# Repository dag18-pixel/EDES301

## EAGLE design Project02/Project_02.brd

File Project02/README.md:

<h1>Etch-A-Sketch Project</h1>
TThis repository contains all implementation files for the Etch-a-Sketch project, including the final PCB layout and schematic, bill of materials (BOM), mechanical drawing, and all library files used. The goal of this project was to apply PCB design concepts from class using Autodesk software and to gain hands-on experience with the PCB manufacturing process

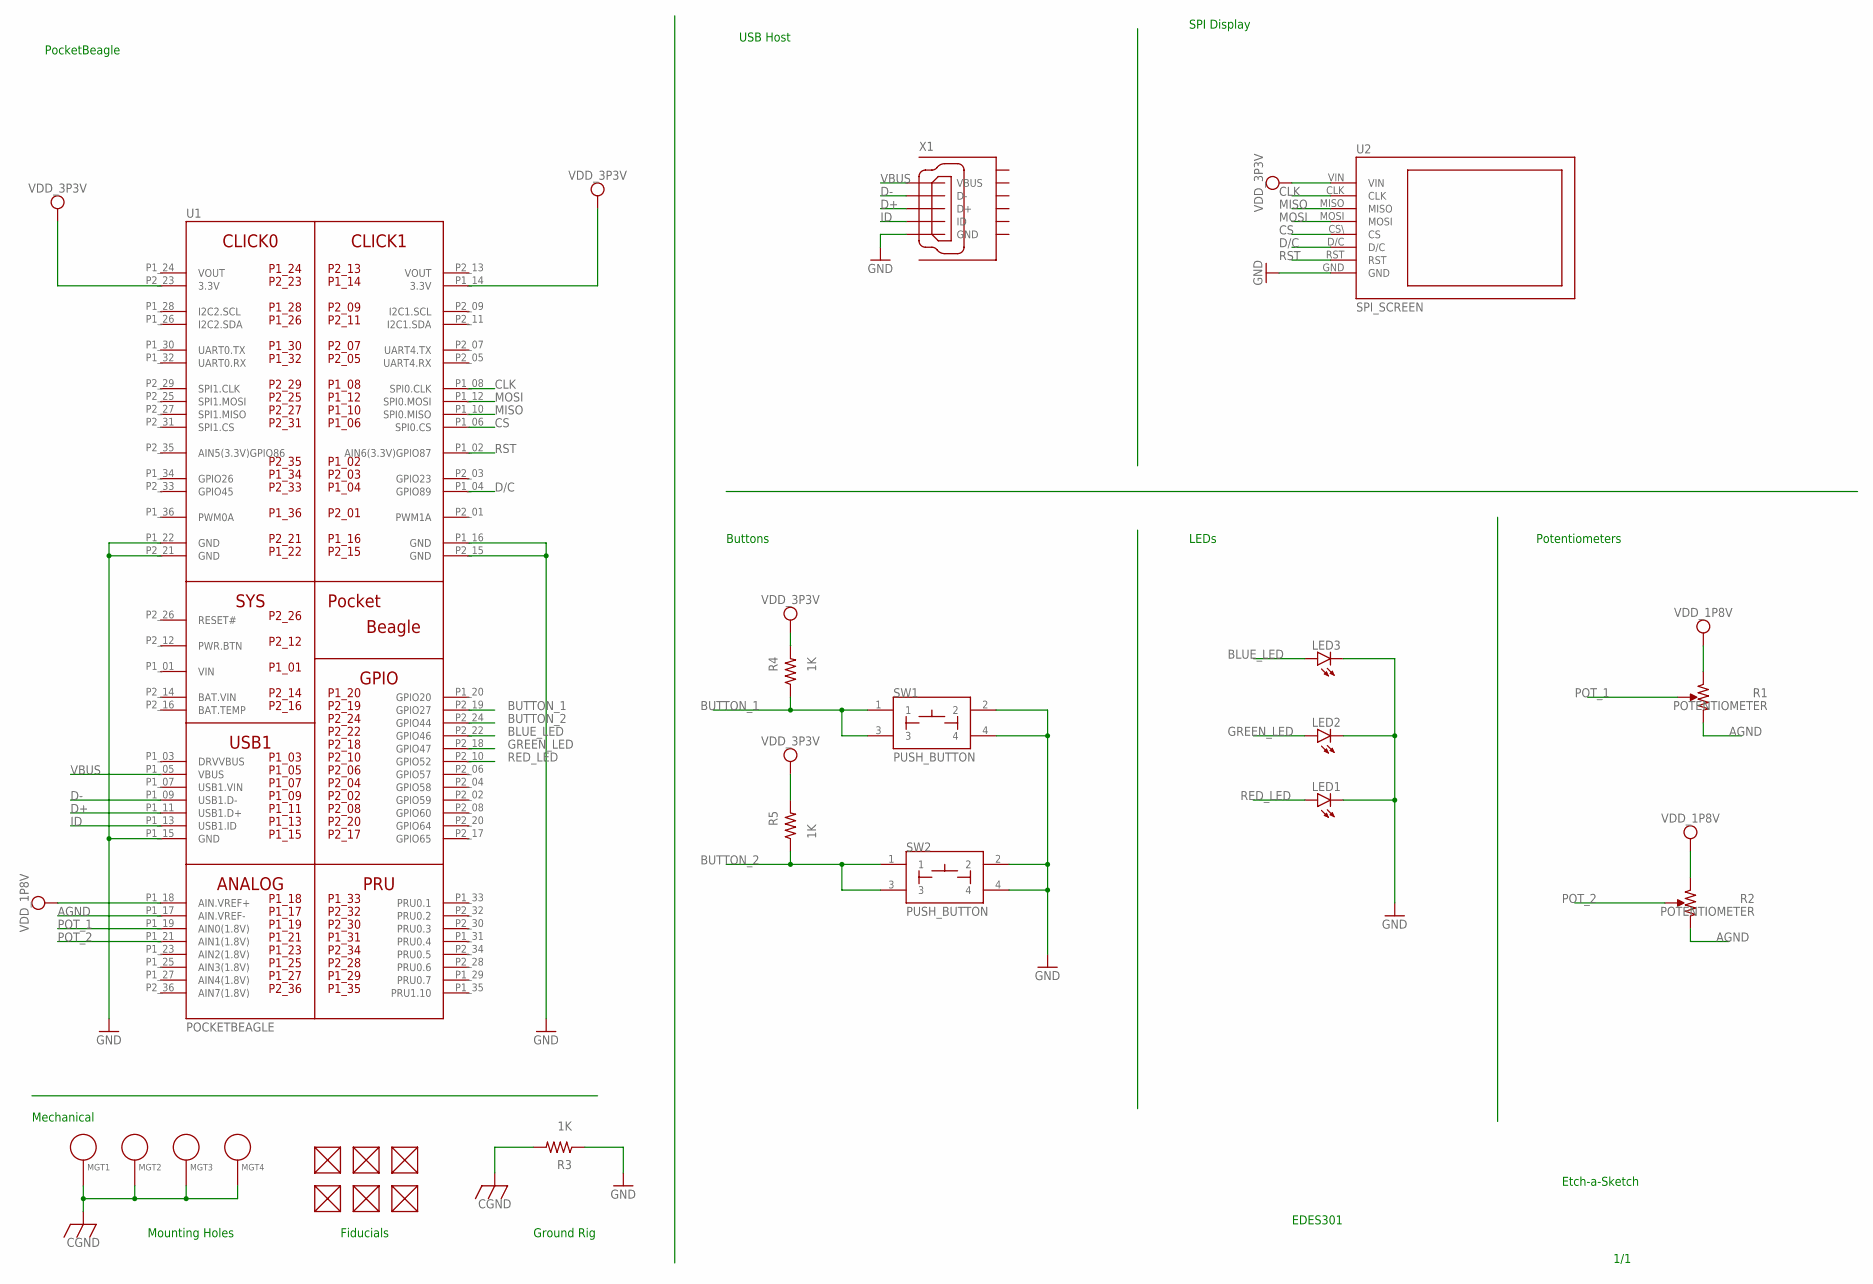
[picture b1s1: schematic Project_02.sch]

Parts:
FUD1, FUD2, FUD3, FUD4, FUD5, FUD6: FIDUCIAL; FIDUCIAL_40MIL
LED1, LED2, LED3: LED-(INCH)-0603; 0603-LED
MGT1, MGT2, MGT3, MGT4: MOUNTING_HOLE
R1, R2: POTENTIOMETER; POT-PO90S
R3, R4, R5: 1K; R0603
SW1, SW2: PUSH_BUTTON; BUTTON_12.5MM
U1: POCKETBEAGLE
U2: SPI_SCREEN; ADAFRUIT-2.8-TFT-SPI-SCREEN
X1: 10118192-0001LF; 10118192-0001LF(MICRO-USB-B-AMPHENOL-FCI)

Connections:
AGND: R1.CW, R2.CW, U1.P1_17 (AIN.VREF-)
BAT.VIN: U1.P2_14 (BAT.VIN)
BLUE_LED: LED3.A, U1.P2_22 (GPIO46)
BUTTON_1: R4.1, SW1.1, SW1.3, U1.P2_19 (GPIO27)
BUTTON_2: R5.1, SW2.1, SW2.3, U1.P2_24 (GPIO44)
CGND: MGT1.P$1, MGT2.P$1, MGT3.P$1, MGT4.P$1, R3.2
CLK: U1.P1_08 (SPI0.CLK), U2.CLK
CS: U1.P1_06 (SPI0.CS), U2.CS\ (CS)
D+: U1.P1_11 (USB1.D+), X1.D+
D-: U1.P1_09 (USB1.D-), X1.D-
D/C: U1.P1_04 (GPIO89), U2.D/C
GND: LED1.K, LED2.K, LED3.K, R3.1, SW1.2, SW1.4, SW2.2, SW2.4, U1.P1_15 (GND), U1.P1_16 (GND), U1.P1_22 (GND), U1.P2_15 (GND), U1.P2_21 (GND), U2.GND, X1.GND
GREEN_LED: LED2.A, U1.P2_18 (GPIO47)
ID: U1.P1_13 (USB1.ID), X1.ID
MISO: U1.P1_10 (SPI0.MISO), U2.MISO
MOSI: U1.P1_12 (SPI0.MOSI), U2.MOSI
POT_1: R1.S, U1.P1_19 (AIN0(1.8V))
POT_2: R2.S, U1.P1_21 (AIN1(1.8V))
RED_LED: LED1.A, U1.P2_10 (GPIO52)
RST: U1.P1_02 (AIN6(3.3V)GPIO87), U2.RST
VBUS: U1.P1_05 (VBUS), X1.VBUS
VDD_1P8V: R1.CCW, R2.CCW, U1.P1_18 (AIN.VREF+)
VDD_3P3V: R4.2, R5.2, U1.P1_14 (3.3V), U1.P2_23 (3.3V), U2.VIN
VIN: U1.P1_01 (VIN)
VOUT: U1.P1_24 (VOUT), U1.P2_13 (VOUT)

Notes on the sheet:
Buttons
LEDs
Potentiometers
USB Host
SPI Display
PocketBeagle
EDES301
1/1
Etch-a-Sketch
Mechanical
Fiducials
Mounting Holes
Ground Rig

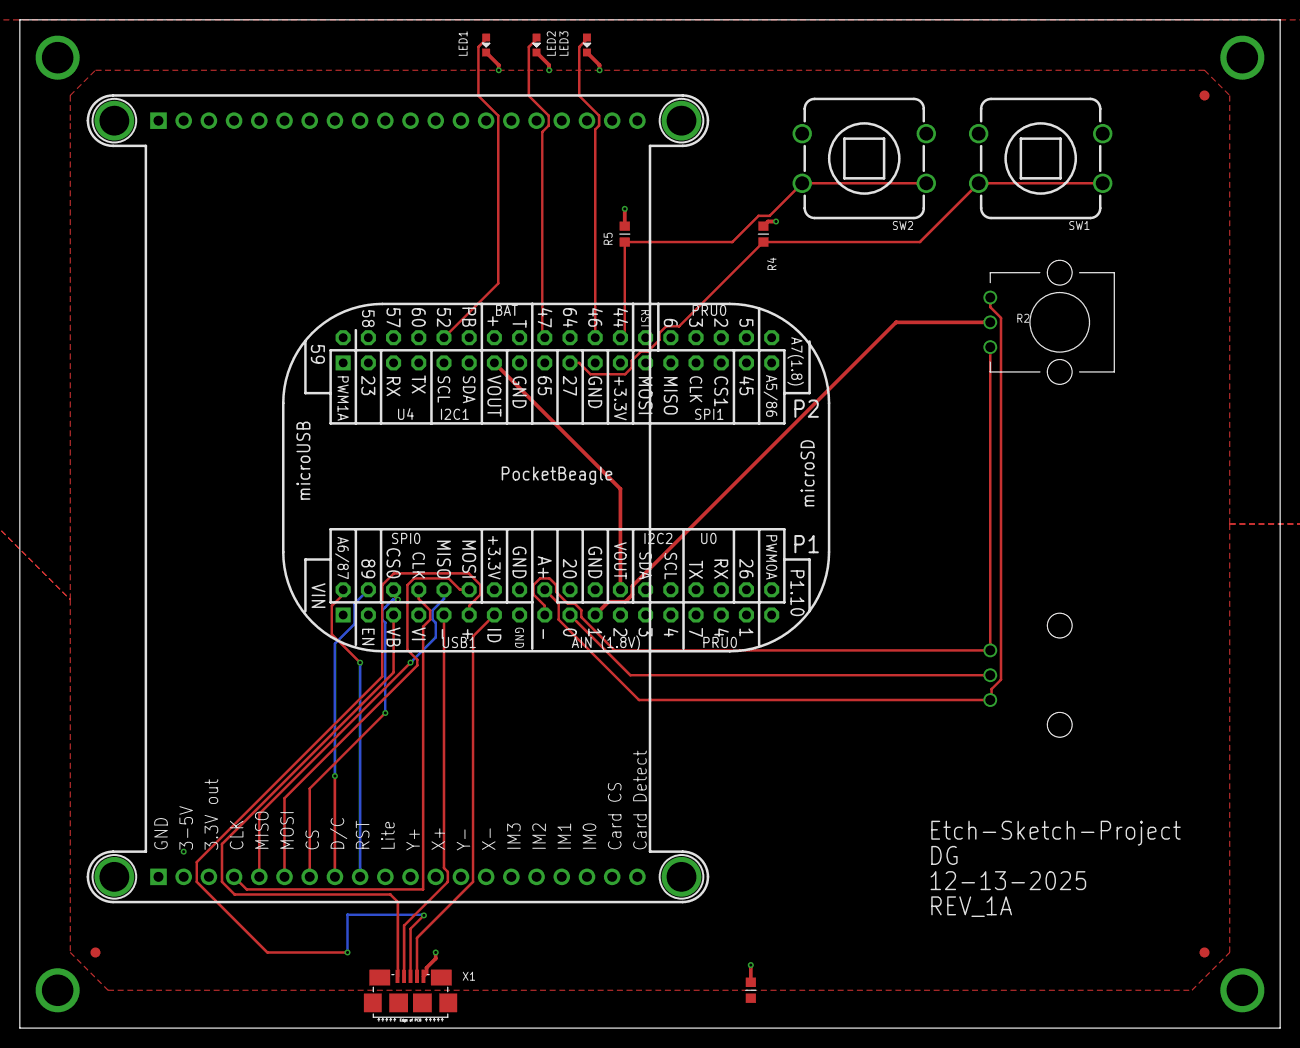
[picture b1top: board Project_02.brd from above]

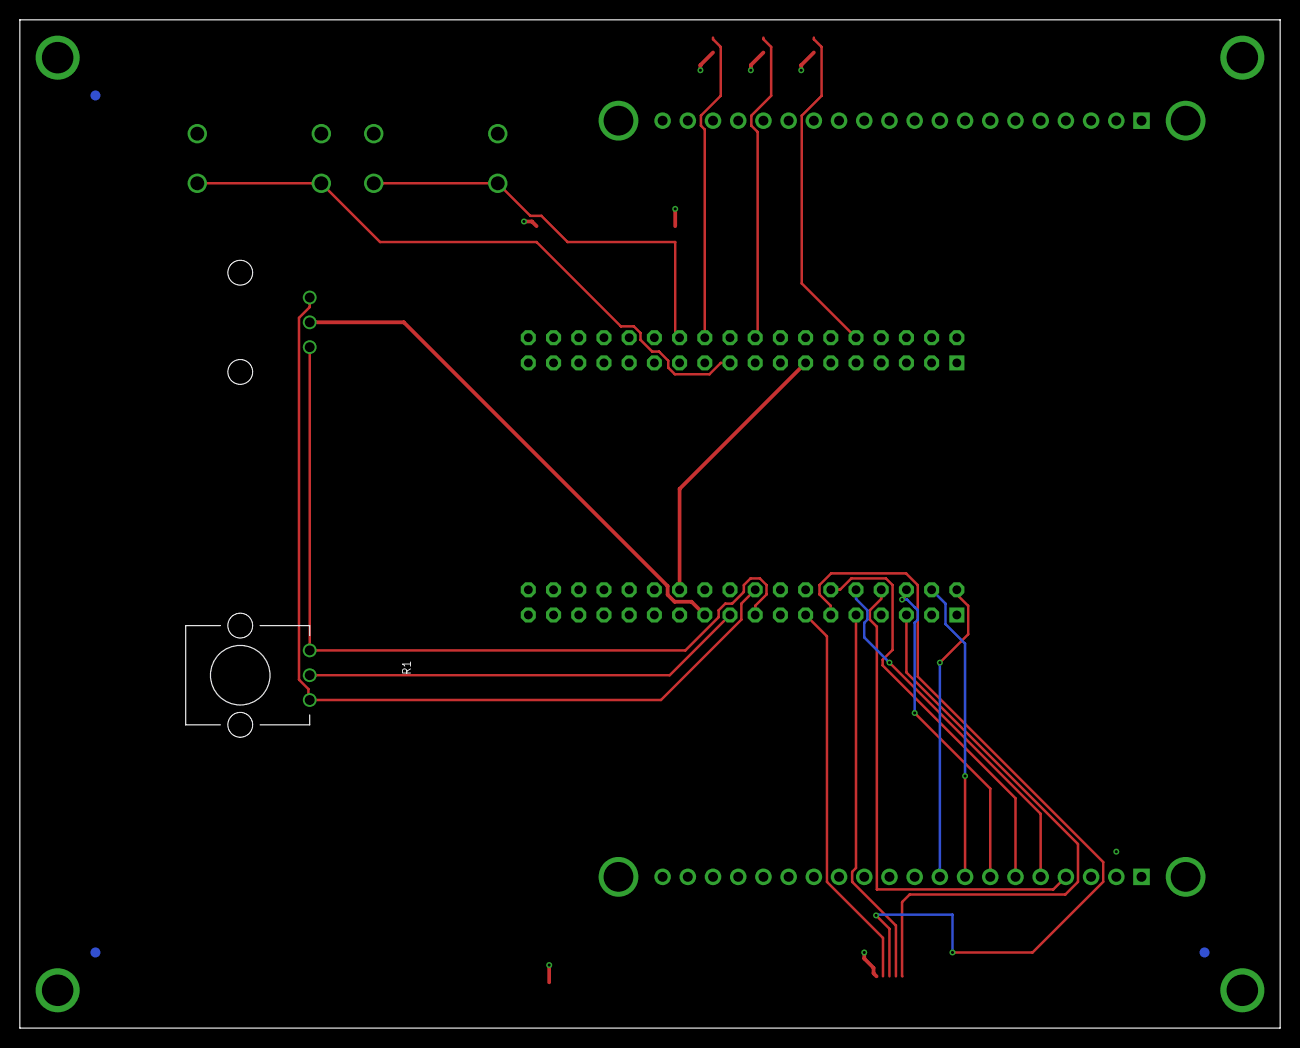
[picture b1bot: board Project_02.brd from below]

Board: 4 copper layers, 127.0 x 101.6 mm, 23 parts (4 on the bottom side), 23 nets.

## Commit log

2025-10-05 Create README.md
    Added READ.md with project title
2025-10-05 Created docs folder
2025-10-05 Added project proposal Powerpoint
2025-10-07 Create simple_calc
2025-10-07 Add simple calculator with new operators and Python
2025-10-07 Added button.py and LED.py
2025-10-24 Added Updated Project Description with software
2025-10-28 added ht16k33.py
2025-11-15 Add initial audio_plot.py script
2025-11-15 Move audio_plot.py into project_01
2025-11-16 Added OLED display and button suport and image plotting
2025-11-27 Worked on finalizing files for project specifically by commenting the OLED.py file that is behind the stethoscope function.
2025-11-28 Added final comments to OLED.py
2025-12-13 Add files via upload
    Added files for project02
2025-12-13 Add files via upload
    Uploaded Eagle files
